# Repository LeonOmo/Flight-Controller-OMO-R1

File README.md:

# Flight-Controller-FC-R1

A Flight Controller, made for rockets, atmospheric data logging and servo control.

## What can it do

- Gyro and Accelerometer: Reads 6 axis motion tracking data using the ICM-45686 IMU.
- Altitude Tracking: Measures barometric pressure and altitude changes with the onboard BMP580 sensor.
- Processing Power: Driven by a STM32F722RETx6.
- 2 Servo Outputs: Dedicated PWM headers to control deployment mechanisms, recovery hatches, or TVC systems.
- Storage: Integrated MicroSD card slot for flight data logging.
- Power Management: Onboard LiPo battery charger circuit combined with a 3.3V Buck regulators for stable voltage delivery.
- Flashing: Hardware BOOT and RESET buttons for code flashing.

## Why does it exist

I really wanted to do something aero hence i havent done anything for it in a while and when i saw the guide for a flightcontroller made for rockets it was just a knight in shining armor.

Learned rotated PCB layout and Zone power delivery in KiCAD.

## BOM

| Component | Function | LCSC number |
| :--- | :--- | :--- |
| STM32F722RET6 | Main Microcontroller | - |
| ICM-45686 | Gyro + Accelorometer | C22459454 |
| BMP580 | High-Accuracy Barometric Pressure Sensor | C22391138 |
| MicroSD Slot | Storage | C91145 |
| TPS63070RNMR |  5V Buck Regulator | C109322 |
| 3.3V Buck Regulator | Voltage Regulator | - |
| BQ25883RGER | Battery Charger  | C544362 |
| USB-C Receptacle | USB-C 16 Pin | C2765186 |

## Tools

- PCB Design: KiCAD
- Reference Guide: Based on a Flightcontroller guide by NotARoomba

## Schematic

## PCB

## Extra

Credits:
- NotARoomba (Guide)
- Omocat (Silkscreen pixelarts only on my PCB not in the files)

## Bonus

Nothing this time around.

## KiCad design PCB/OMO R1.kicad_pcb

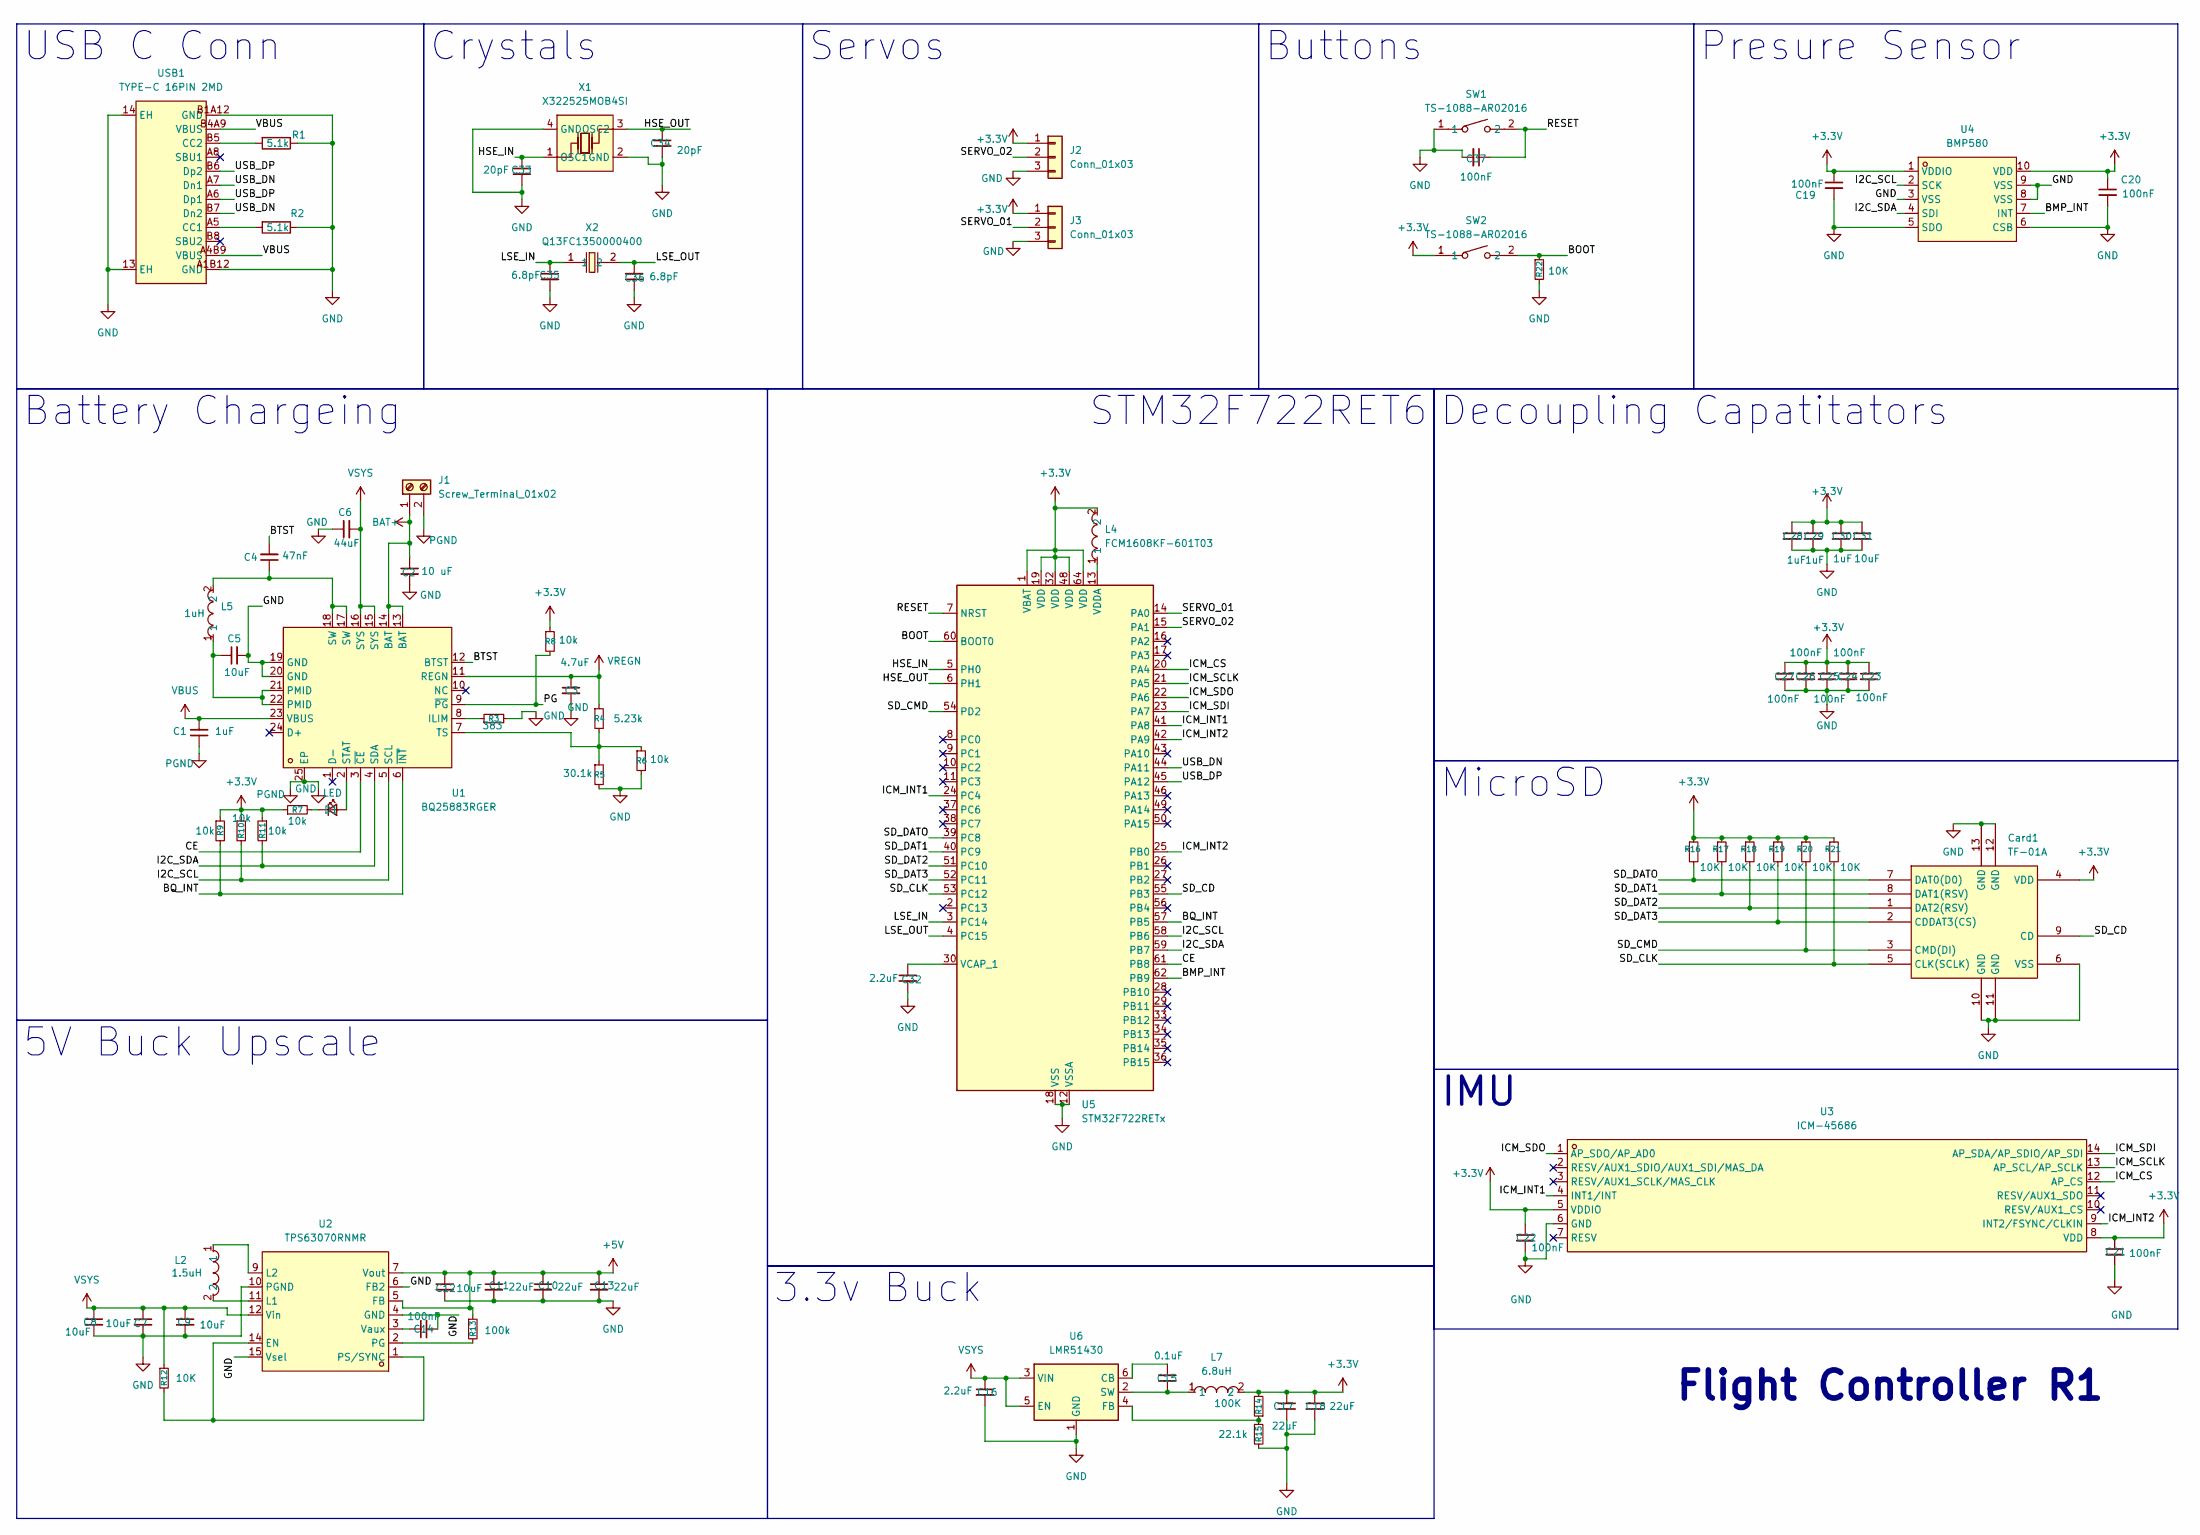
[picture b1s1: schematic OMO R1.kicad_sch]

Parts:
C1, C28, C29, C30: 1uF; C_0402_1005Metric
C2: 10 uF; C_0603_1608Metric
C3: 4.7uF; C_0402_1005Metric
C4: 47nF; C_0402_1005Metric
C5, C31: 10uF; C_0402_1005Metric
C6: 44uF; C_0603_1608Metric
C7, C8: 10uF; C_0805_2012Metric
C9, C12: 10uF; C_0603_1608Metric
C10, C11, C13, C17, C18: 22uF; C_0805_2012Metric
C14, C19, C20, C21, C22, C37: 100nF; C_0402_1005Metric
C15: 0.1uF; C_0402_1005Metric
C16: 2.2uF; C_0603_1608Metric
C23: 100nF; C_0201_0603Metric_Pad0.64x0.40mm_HandSolder
C24, C25, C26, C27: 100nF; C_0201_0603Metric
C32: 2.2uF; C_0201_0603Metric
C33, C34: 20pF; C_0402_1005Metric
C35, C36: 6.8pF; C_0402_1005Metric
Card1: TF-01A; TF-SMD_TF-01A; MPN TF-01A; LCSC Part C91145
D1: LED; LED_0402_1005Metric
J1: Screw_Terminal_01x02; TerminalBlock_Xinya_XY308-2.54-2P_1x02_P2.54mm_Horizontal
J2, J3: Conn_01x03; PinHeader_1x03_P2.54mm_Vertical
L2: 1.5uH; IND-SMD_L4.0-W4.0-A; MPN XFL4020-152MEC; LCSC Part C3033018
L4: FCM1608KF-601T03; L0603; MPN FCM1608KF-601T03; LCSC Part C141723
L5: 1uH; L2520; MPN DFE252012F-1R0M=P2; LCSC Part C435392
L7: 6.8uH; IND-SMD_L3.0-W3.0; MPN YHNR3015-5R6M; LCSC Part C18236327
R1, R2: 5.1k; R_0201_0603Metric
R3: 383; R_0201_0603Metric
R4: 5.23k; R_0201_0603Metric
R5: 30.1k; R_0201_0603Metric
R6, R7, R8, R9, R10, R11: 10k; R_0201_0603Metric
R12, R16, R17, R18, R19, R20, R21, R22: 10K; R_0201_0603Metric
R13: 100k; R_0402_1005Metric
R14: 100K; R_0402_1005Metric
R15: 22.1k; R_0402_1005Metric
SW1, SW2: TS-1088-AR02016; SW-SMD_L3.9-W3.0-P4.45; MPN TS-1088-AR02016; LCSC Part C720477
U1: BQ25883RGER; VFQFPN-24_L4.0-W4.0-P0.50-BL-EP2.8; MPN BQ25883RGER; LCSC Part C544362
U2: TPS63070RNMR; VQFN-15_L3.0-W2.5-P0.50-BL; MPN TPS63070RNMR; LCSC Part C109322
U3: ICM-45686; LGA-14_L3.0-W2.5-P0.50-TL; MPN ICM-45686; LCSC Part C22459454
U4: BMP580; LGA-10_L2.0-W2.0-P0.50-TL_BMP580; MPN BMP580; LCSC Part C22391138
U5: STM32F722RETx; LQFP-64_10x10mm_P0.5mm
U6: LMR51430; SOT-23-6
USB1: TYPE-C 16PIN 2MD; USB-C-SMD_TYPE-C-16PIN-2MD-073; MPN TYPE-C 16PIN 2MD(073); LCSC Part C2765186
X1: X322525MOB4SI; CRYSTAL-SMD_4P-L3.2-W2.5-BL; MPN X322525MOB4SI; LCSC Part C9006
X2: Q13FC1350000400; FC-135R_L3.2-W1.5; MPN Q13FC13500004; LCSC Part C32346

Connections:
+5V: C10.1, C11.1, C12.1, C13.1, R13.1, U2.5 (FB), U2.7 (Vout)
/BMP_INT: U4.7 (INT), U5.62 (PB9)
/BOOT: R22.1, SW2.2, U5.60 (BOOT0); also elsewhere on the board
/BQ_INT: R9.2, U1.6 (~INT), U5.57 (PB5)
/BTST: C4.2, U1.12 (BTST)
/CE: U1.3 (~CE), U5.61 (PB8)
/HSE_IN: C33.1, U5.5 (PH0), X1.1 (OSC1)
/HSE_OUT: C34.1, U5.6 (PH1), X1.3 (OSC2)
/I2C_SCL: R10.2, U1.5 (SCL), U4.2 (SCK), U5.58 (PB6)
/I2C_SDA: R11.2, U1.4 (SDA), U4.4 (SDI), U5.59 (PB7)
/ICM_CS: U3.12 (AP_CS), U5.20 (PA4)
/ICM_INT1: U3.4 (INT1/INT), U5.24 (PC4), U5.41 (PA8)
/ICM_INT2: U3.9 (INT2/FSYNC/CLKIN), U5.25 (PB0), U5.42 (PA9)
/ICM_SCLK: U3.13 (AP_SCL/AP_SCLK), U5.21 (PA5)
/ICM_SDI: U3.14 (AP_SDA/AP_SDIO/AP_SDI), U5.23 (PA7)
/ICM_SDO: U3.1 (AP_SDO/AP_AD0), U5.22 (PA6)
/LSE_IN: C35.1, U5.3 (PC14), X2.1
/LSE_OUT: C36.2, U5.4 (PC15), X2.2
/PG: R8.2, U1.9 (~PG)
/RESET: C37.1, SW1.2, U5.7 (NRST); also elsewhere on the board
/SD_CD: Card1.9 (CD), U5.55 (PB3)
/SD_CLK: Card1.5 (CLK(SCLK)), R21.2, U5.53 (PC12)
/SD_CMD: Card1.3 (CMD(DI)), R20.2, U5.54 (PD2)
/SD_DAT1: Card1.8 (DAT1(RSV)), R17.2, U5.40 (PC9)
/SD_DAT2: Card1.1 (DAT2(RSV)), R18.2, U5.51 (PC10)
/SD_DAT3: Card1.2 (CDDAT3(CS)), R19.2, U5.52 (PC11)
/SD_DATO: Card1.7 (DAT0(D0)), R16.2, U5.39 (PC8)
/SERVO_01: J3.2, U5.14 (PA0)
/SERVO_02: J2.2, U5.15 (PA1)
/USB_DN: U5.44 (PA11), USB1.A7 (Dn1), USB1.B7 (Dn2)
/USB_DP: U5.45 (PA12), USB1.A6 (Dp1), USB1.B6 (Dp2)
BAT+: C2.1, J1.1, U1.13 (BAT), U1.14 (BAT)
GND: C1.1, C2.2, C3.2, C5.2, C6.1, C7.2, C8.2, C9.2, C10.2, C11.2, C12.2, C13.2, C14.2, C16.2, C17.2, C18.2, C19.2, C20.2, C21.2, C22.2, C23.2, C24.2, C25.2, C26.2, C27.2, C28.2, C29.2, C30.2, C31.2, C32.2, C33.2, C34.2, C35.2, C36.1, C37.2, Card1.6 (VSS), Card1.10 (GND), Card1.11 (GND), Card1.12 (GND), Card1.13 (GND), J1.2, J2.3, J3.3, R1.1, R2.1, R3.2, R5.2, R6.2, R15.2, R22.2, SW1.1, U1.19 (GND), U1.20 (GND), U1.25 (EP), U2.4 (GND), U2.6 (FB2), U2.10 (PGND), U2.15 (Vsel), U3.6 (GND), U4.3 (VSS), U4.5 (SDO), U4.6 (CSB), U4.8 (VSS), U4.9 (VSS), U5.12 (VSSA), U5.18 (VSS), U5.31 (VSS), U5.47 (VSS), U5.63 (VSS), U6.1 (GND), USB1.13 (EH), USB1.14 (EH), USB1.A1B12 (GND), USB1.B1A12 (GND), X1.2 (GND), X1.4 (GND); also elsewhere on the board
unnamed: C4.1, L5.2, U1.17 (SW), U1.18 (SW)
unnamed: C5.1, L5.1, U1.21 (PMID), U1.22 (PMID)
unnamed: D1.2 (A), U1.2 (STAT)
unnamed: D1.1 (K), R7.2
unnamed: R3.1, U1.8 (ILIM)
unnamed: R4.2, R5.1, R6.1, U1.7 (TS)
unnamed: R12.2, U2.1 (PS/SYNC), U2.14 (EN)
unnamed: L2.2, U2.11 (L1)
unnamed: L2.1, U2.9 (L2)
unnamed: R13.2, U2.2 (PG)
unnamed: C14.1, U2.3 (Vaux)
unnamed: C32.1, U5.30 (VCAP_1)
unnamed: L4.1, U5.13 (VDDA)
unnamed: C15.1, U6.6 (CB)
unnamed: R14.1, R15.1, U6.4 (FB)
unnamed: R2.2, USB1.A5 (CC1)
unnamed: R1.2, USB1.B5 (CC2)
VBUS: C1.2, U1.23 (VBUS), USB1.A4B9 (VBUS), USB1.B4A9 (VBUS)
VREGN: C3.1, R4.1, U1.11 (REGN)
VSYS: C6.2, C7.1, C8.1, C9.1, C16.1, R12.1, U1.15 (SYS), U1.16 (SYS), U2.12 (Vin), U6.3 (VIN), U6.5 (EN)

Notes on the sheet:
Flight Controller R1
STM32F722RET6
Servos
3.3v Buck
Presure Sensor
Crystals
MicroSD
Decoupling Capatitators
5V Buck Upscale
Buttons
USB C Conn
Battery Chargeing
IMU

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
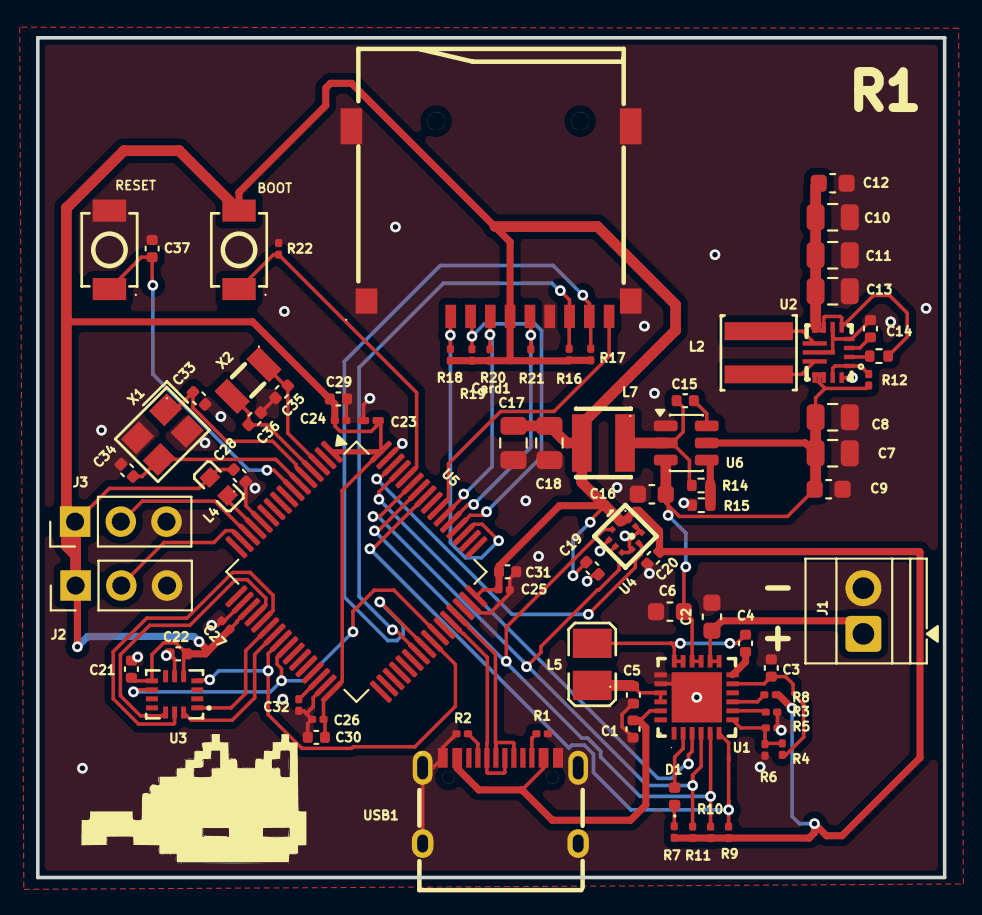
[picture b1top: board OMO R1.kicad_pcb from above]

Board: 2 copper layers, 50.4 x 46.7 mm, 79 parts (0 on the bottom side), 55 nets.

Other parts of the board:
BOOT: TS-1088-AR02016; SW-SMD_L3.9-W3.0-P4.45
RESET: TS-1088-AR02016; SW-SMD_L3.9-W3.0-P4.45

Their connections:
/BOOT: BOOT.2; also elsewhere on the board
/RESET: RESET.2; also elsewhere on the board
GND: RESET.1; also elsewhere on the board

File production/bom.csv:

Designator,Footprint,Quantity,Value,LCSC Part #
"BOOT, RESET",SW-SMD_L3.9-W3.0-P4.45,2,TS-1088-AR02016,C720477
"C1, C28, C29, C30",0402,4,1uF,
"C10, C11, C13, C17, C18",0805,5,22uF,
"C12, C9",0603,2,10uF,
"C14, C19, C20, C21, C22, C37",0402,6,100nF,
C15,0402,1,0.1uF,
C16,0603,1,2.2uF,
C2,0603,1,10 uF,
"C23, C24, C25, C26, C27",0201,5,100nF,
C3,0402,1,4.7uF,
"C31, C5",0402,2,10uF,
C32,0201,1,2.2uF,
"C33, C34",0402,2,20pF,
"C35, C36",0402,2,6.8pF,
C4,0402,1,47nF,
C6,0603,1,44uF,
"C7, C8",0805,2,10uF,
CARD1,TF-SMD_TF-01A,1,TF-01A,C91145
D1,0402,1,LED,
J1,TerminalBlock_Xinya_XY308-2.54-2P_1x02_P2.54mm_Horizontal,1,Screw_Terminal_01x02,
"J2, J3",PinHeader_1x03_P2.54mm_Vertical,2,Conn_01x03,
L2,IND-SMD_L4.0-W4.0-A,1,1.5uH,C3033018
L4,L0603,1,FCM1608KF-601T03,C141723
L5,L2520,1,1uH,C435392
L7,IND-SMD_L3.0-W3.0,1,6.8uH,C18236327
"R1, R2",0201,2,5.1k,
"R10, R11, R12, R16, R17, R18, R19, R20, R21, R22, R6, R7, R8, R9",0201,14,10k,
"R13, R14",0402,2,100k,
R15,0402,1,22.1k,
R3,0201,1,383,
R4,0201,1,5.23k,
R5,0201,1,30.1k,
U1,VFQFPN-24_L4.0-W4.0-P0.50-BL-EP2.8,1,BQ25883RGER,C544362
U2,VQFN-15_L3.0-W2.5-P0.50-BL,1,TPS63070RNMR,C109322
U3,LGA-14_L3.0-W2.5-P0.50-TL,1,ICM-45686,C22459454
U4,LGA-10_L2.0-W2.0-P0.50-TL_BMP580,1,BMP580,C22391138
U5,LQFP-64_10x10mm_P0.5mm,1,STM32F722RETx,
U6,SOT-23-6,1,LMR51430,
USB1,USB-C-SMD_TYPE-C-16PIN-2MD-073,1,TYPE-C 16PIN 2MD,C2765186
X1,CRYSTAL-SMD_4P-L3.2-W2.5-BL,1,X322525MOB4SI,C9006
X2,FC-135R_L3.2-W1.5,1,Q13FC1350000400,C32346
